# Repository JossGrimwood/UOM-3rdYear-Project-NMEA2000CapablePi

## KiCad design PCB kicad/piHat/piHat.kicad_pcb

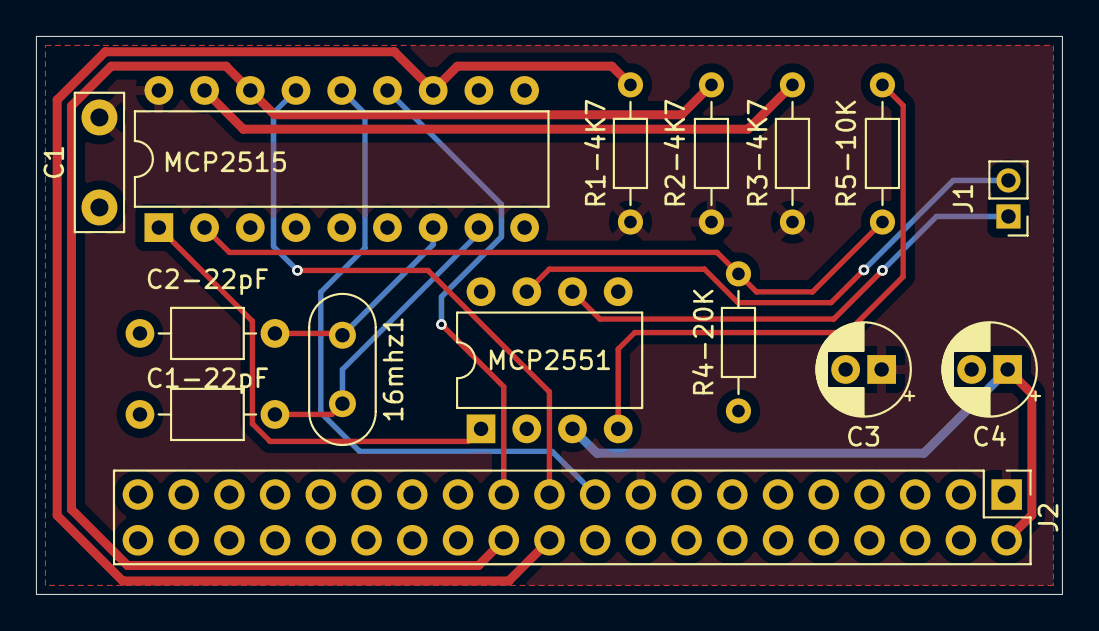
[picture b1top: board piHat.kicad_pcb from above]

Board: 2 copper layers, 57.0 x 31.0 mm, 15 parts (0 on the bottom side), 16 nets.

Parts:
16mhz1: 16MHZ; Crystal_HC52-6mm_Vertical
C1: C; C_Disc_D7.5mm_W2.5mm_P5.00mm
C1-22pF, C2-22pF: C22pF; C_Axial_L3.8mm_D2.6mm_P7.50mm_Horizontal
C3, C4: C_Polarized; CP_Radial_D5.0mm_P2.00mm
J1: Conn_01x02_Pin; PinHeader_1x02_P2.00mm_Vertical
J2: Raspberry_Pi_2_3; PinHeader_2x20_P2.54mm_Vertical
MCP2515: MCP2515-xSO; DIP-18_W7.62mm
MCP2551: MCP2551-I-P; DIP-8_W7.62mm
R1-4K7, R2-4K7: R4K7; R_Axial_DIN0204_L3.6mm_D1.6mm_P7.62mm_Horizontal
R3-4K7: R; R_Axial_DIN0204_L3.6mm_D1.6mm_P7.62mm_Horizontal
R4-20K: R20K; R_Axial_DIN0204_L3.6mm_D1.6mm_P7.62mm_Horizontal
R5-10K: R10K; R_Axial_DIN0204_L3.6mm_D1.6mm_P7.62mm_Horizontal

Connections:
unnamed: J1.1, MCP2551.6 (CANL)
unnamed: J1.2, MCP2551.7 (CANH)
unnamed: J2.22 (GPIO25), MCP2515.12 (~INT), R1-4K7.2
unnamed: J2.21 (MISO0/GPIO9), MCP2515.15 (SO)
unnamed: J2.19 (MOSI0/GPIO10), MCP2515.14 (SI)
unnamed: J2.23 (SCLK0/GPIO11), MCP2515.13 (SCK)
unnamed: J2.24 (~CE0/GPIO8), MCP2515.16 (~CS), R2-4K7.1
unnamed: 16mhz1.2, C1-22pF.1, MCP2515.8 (OSC1)
unnamed: 16mhz1.1, C2-22pF.1, MCP2515.7 (OSC2)
unnamed: MCP2515.2 (RXCAN), R4-20K.2, R5-10K.2
unnamed: MCP2515.1 (TXCAN), MCP2551.1 (TXD)
unnamed: MCP2515.17 (~RESET), R3-4K7.2
unnamed: MCP2551.4 (RXD), R5-10K.1
VCC: C1.2, C3.1, J2.1 (3V3), J2.17 (3V3), MCP2515.18 (VDD), R1-4K7.1, R2-4K7.2, R3-4K7.1
VDD: C4.1, J2.2 (5V), J2.4 (5V), MCP2551.3 (VDD)
VSS: C1.1, C1-22pF.2, C2-22pF.2, C3.2, C4.2, J2.6 (GND), J2.9 (GND), J2.14 (GND), J2.20 (GND), J2.25 (GND), J2.30 (GND), J2.34 (GND), J2.39 (GND), MCP2515.9 (VSS), MCP2551.2 (VSS), MCP2551.8 (Rs), R4-20K.1

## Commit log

2024-11-04 Project
2024-11-04 Add submodule
